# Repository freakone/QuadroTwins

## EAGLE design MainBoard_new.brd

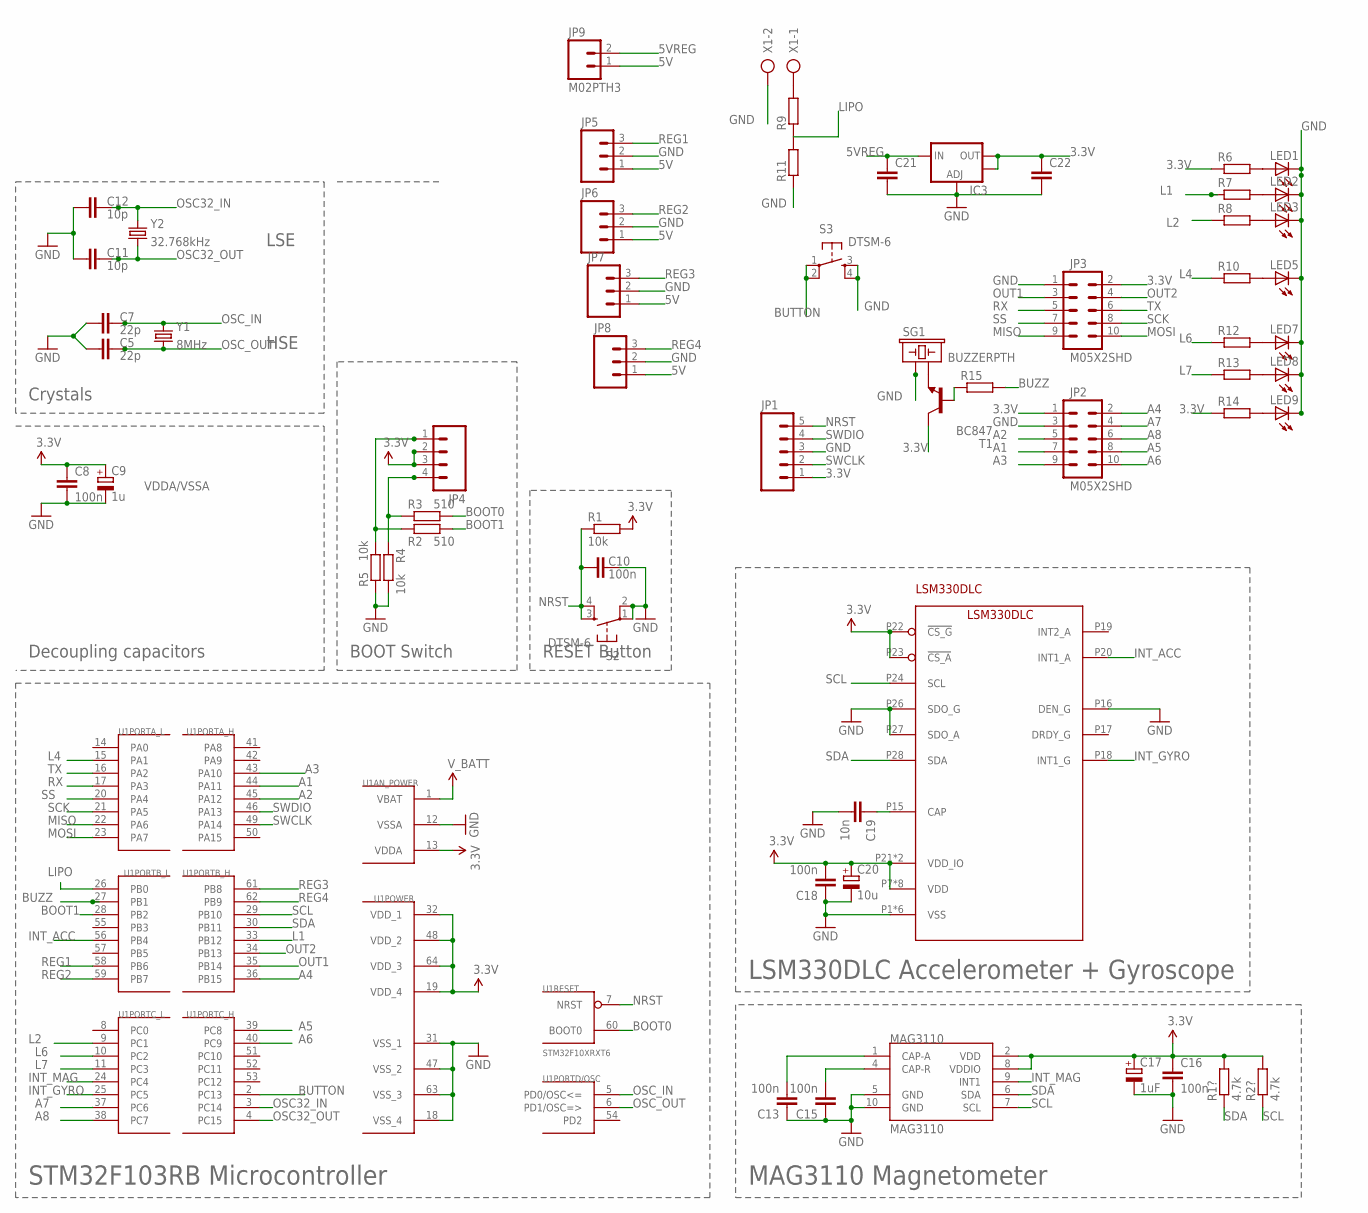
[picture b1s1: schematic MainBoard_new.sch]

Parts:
C5, C7: 22p; C0805
C8, C10, C13, C15, C16, C18: 100n; C0805
C9: 1u; SMC_A
C11, C12: 10p; C0805
C17: 1uF; SMC_A
C19: 10n; C0805
C20: 10u; SMC_A
C21, C22: C-EUC0805; C0805
IC3: V_REG_LM1117SOT223; SOT223
JP1: M05PTH_LONGPADS; 1X05_LONGPADS
JP2, JP3: M05X2SHD; 2X5-SHROUDED
JP4: M04LONGPADS; 1X04_LONGPADS
JP5, JP6, JP7, JP8: M03LONGPADS; 1X03_LONGPADS
JP9: M02PTH3; 1X02_LONGPADS
LED1, LED2, LED3, LED5, LED7, LED8, LED9: LEDCHIPLED_0805; CHIPLED_0805
LSM330DLC: LSM330DLC; LGA_4X5X1P1_28L
MAG3110: MAG3110; DFN-10
R1, R4, R5: 10k; R0805
R1?, R2?: 4.7k; R0805
R2, R3: 510; R0805
R6, R7, R8, R9, R10, R11, R12, R13, R14: R-EU_M0805; M0805
R15: R-EU_R0805; R0805
S2, S3: DTSM-6
SG1: BUZZERPTH; BUZZER-12MM
T1: BC847; SOT23
U1: STM32F10XRXT6; TQFP64
X1: AK300/2
Y1: 8MHz; HC49UP
Y2: 32.768kHz; CRYSTAL-32KHZ-SMD_EPSON_MC146

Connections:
3.3V: C8.1, C9.+, C16.1, C17.+, C18.2, C20.+, C22.1, IC3.2 (OUT), IC3.4 (OUT), JP1.1, JP2.1, JP3.2, JP4.2, JP4.3, LSM330DLC.P7 (VDD), LSM330DLC.P8 (VDD), LSM330DLC.P9 (VDD), LSM330DLC.P10 (VDD), LSM330DLC.P11 (VDD), LSM330DLC.P12 (VDD), LSM330DLC.P13 (VDD), LSM330DLC.P14 (VDD), LSM330DLC.P21 (VDD_IO), LSM330DLC.P22 (!CS_G), LSM330DLC.P23 (!CS_A), LSM330DLC.P25 (VDD_IO), MAG3110.2 (VDD), MAG3110.8 (VDDIO), R1.2, R1?.2, R2?.2, R6.1, R14.1, T1.3 (C), U1.13 (VDDA), U1.19 (VDD_4), U1.32 (VDD_1), U1.48 (VDD_2), U1.64 (VDD_3)
5V: JP5.1, JP6.1, JP7.1, JP8.1, JP9.1
5VREG: C21.1, IC3.3 (IN), JP9.2
A1: JP2.7, U1.44 (PA11)
A2: JP2.5, U1.45 (PA12)
A3: JP2.9, U1.43 (PA10)
A4: JP2.2, U1.36 (PB15)
A5: JP2.8, U1.39 (PC8)
A6: JP2.10, U1.40 (PC9)
A7: JP2.4, U1.37 (PC6)
A8: JP2.6, U1.38 (PC7)
BOOT0: R3.2, U1.60 (BOOT0)
BOOT1: R2.2, U1.28 (PB2)
BUTTON: S3.1, S3.2, U1.2 (PC13)
BUZZ: R15.2, U1.27 (PB1)
GND: C5.1, C7.1, C8.2, C9.-, C10.2, C11.1, C12.1, C13.1, C15.1, C16.2, C17.-, C18.1, C19.2, C20.-, C21.2, C22.2, IC3.1 (ADJ), JP1.3, JP2.3, JP3.1, JP5.2, JP6.2, JP7.2, JP8.2, LED1.C, LED2.C, LED3.C, LED5.C, LED7.C, LED8.C, LED9.C, LSM330DLC.P1 (VSS), LSM330DLC.P2 (VSS), LSM330DLC.P3 (VSS), LSM330DLC.P4 (VSS), LSM330DLC.P5 (VSS), LSM330DLC.P6 (VSS), LSM330DLC.P16 (DEN_G), LSM330DLC.P26 (SDO_G), LSM330DLC.P27 (SDO_A), MAG3110.5 (GND), MAG3110.10 (GND), R4.2, R5.1, R11.1, S2.1, S2.2, S3.3, S3.4, SG1.+ (1), U1.12 (VSSA), U1.18 (VSS_4), U1.31 (VSS_1), U1.47 (VSS_2), U1.63 (VSS_3), X1.2
INT_ACC: LSM330DLC.P20 (INT1_A), U1.56 (PB4)
INT_GYRO: LSM330DLC.P18 (INT1_G), U1.25 (PC5)
INT_MAG: MAG3110.9 (INT1), U1.24 (PC4)
L1: R7.1, U1.33 (PB12)
L2: R8.1, U1.9 (PC1)
L4: R10.1, U1.15 (PA1)
L6: R12.1, U1.10 (PC2)
L7: R13.1, U1.11 (PC3)
LIPO: R9.1, R11.2, U1.26 (PB0)
MISO: JP3.9, U1.22 (PA6)
MOSI: JP3.10, U1.23 (PA7)
unnamed: JP4.1, R2.1, R5.2
unnamed: JP4.4, R3.1, R4.1
unnamed: C15.2, MAG3110.4 (CAP-R)
unnamed: C13.2, MAG3110.1 (CAP-A)
unnamed: C19.1, LSM330DLC.P15 (CAP)
unnamed: LED1.A, R6.2
unnamed: LED2.A, R7.2
unnamed: LED3.A, R8.2
unnamed: LED5.A, R10.2
unnamed: LED7.A, R12.2
unnamed: LED8.A, R13.2
unnamed: LED9.A, R14.2
unnamed: SG1.- (2), T1.2 (E)
unnamed: R9.2, X1.1
unnamed: R15.1, T1.1 (B)
NRST: C10.1, JP1.5, R1.1, S2.3, S2.4, U1.7 (NRST)
OSC32_IN: C12.2, U1.3 (PC14), Y2.P$1 (2)
OSC32_OUT: C11.2, U1.4 (PC15), Y2.P$2 (1)
OSC_IN: C7.2, U1.5 (PD0/OSC<=), Y1.2
OSC_OUT: C5.2, U1.6 (PD1/OSC=>), Y1.1
OUT1: JP3.3, U1.35 (PB14)
OUT2: JP3.4, U1.34 (PB13)
REG1: JP5.3, U1.58 (PB6)
REG2: JP6.3, U1.59 (PB7)
REG3: JP7.3, U1.61 (PB8)
REG4: JP8.3, U1.62 (PB9)
RX: JP3.5, U1.17 (PA3)
SCK: JP3.8, U1.21 (PA5)
SCL: LSM330DLC.P24 (SCL), MAG3110.7 (SCL), R2?.1, U1.29 (PB10)
SDA: LSM330DLC.P28 (SDA), MAG3110.6 (SDA), R1?.1, U1.30 (PB11)
SS: JP3.7, U1.20 (PA4)
SWCLK: JP1.2, U1.49 (PA14)
SWDIO: JP1.4, U1.46 (PA13)
TX: JP3.6, U1.16 (PA2)
V_BATT: U1.1 (VBAT)

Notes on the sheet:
STM32F103RB Microcontroller
RESET Button
BOOT Switch
Decoupling capacitors
VDDA/VSSA
Crystals
HSE
LSE
MAG3110 Magnetometer
LSM330DLC Accelerometer + Gyroscope

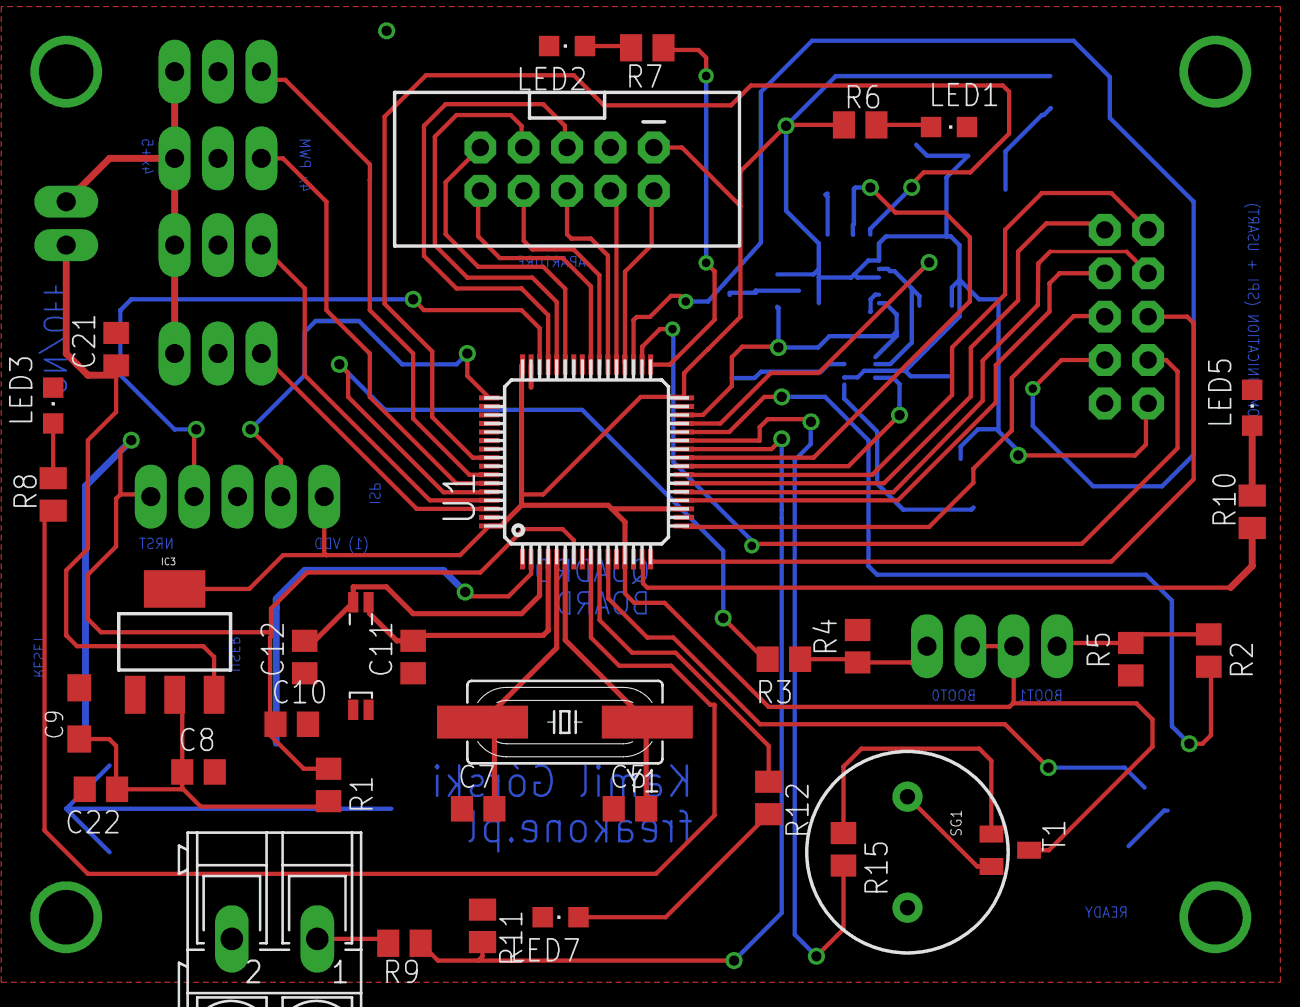
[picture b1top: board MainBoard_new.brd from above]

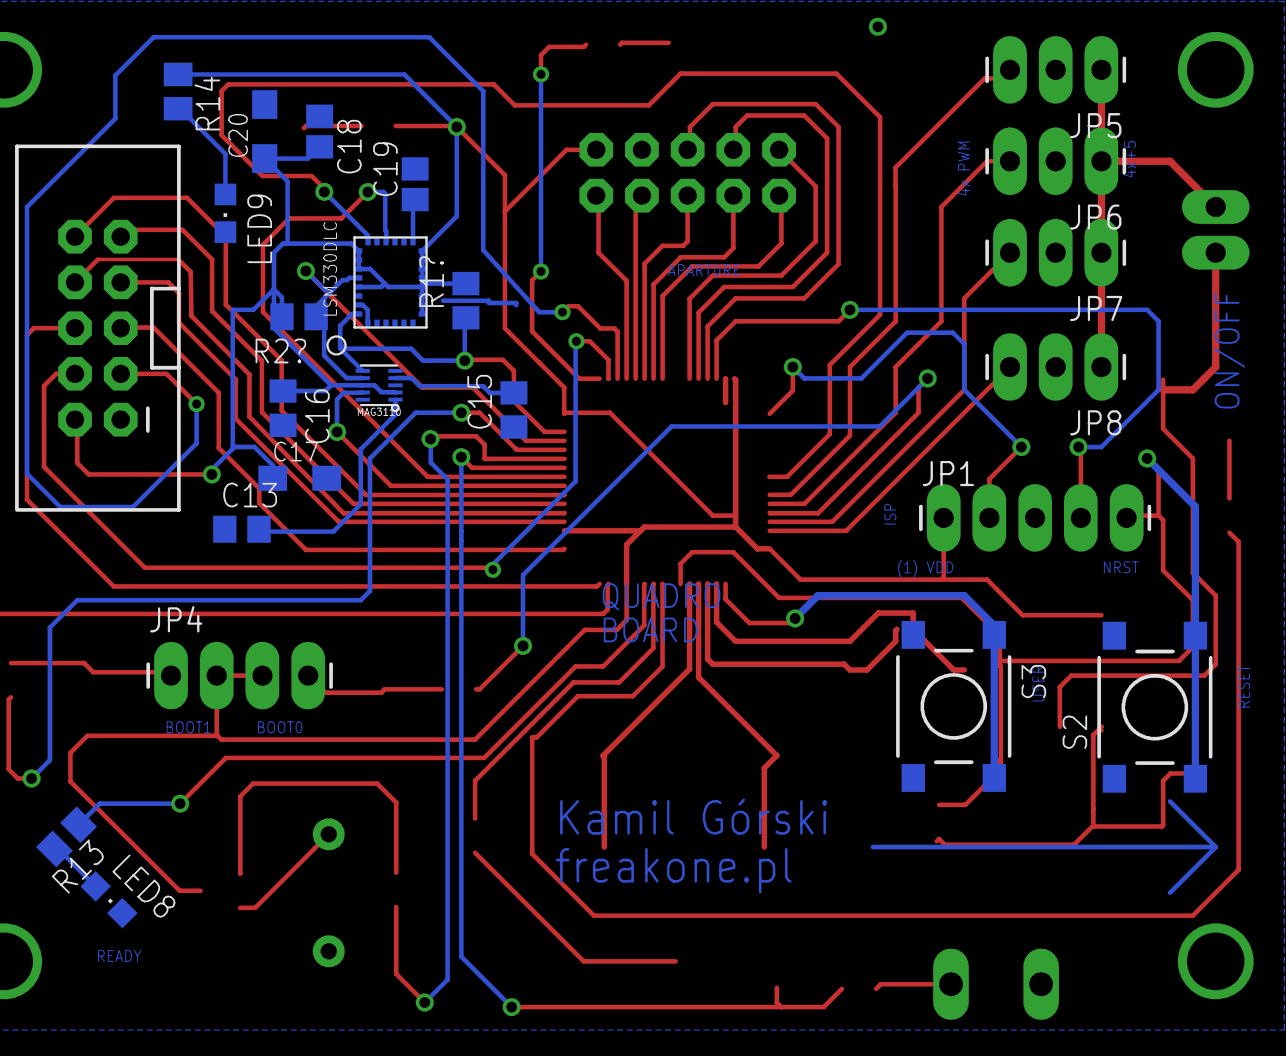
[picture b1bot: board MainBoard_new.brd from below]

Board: 2 copper layers, 60 parts (24 on the bottom side), 61 nets.

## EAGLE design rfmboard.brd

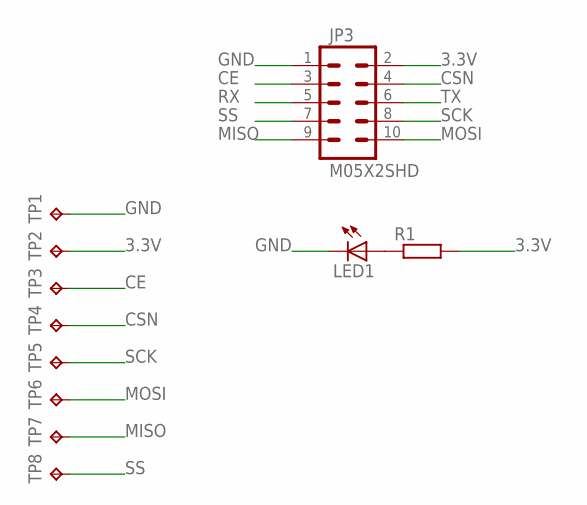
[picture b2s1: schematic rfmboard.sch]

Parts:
JP3: M05X2SHD; 2X5-SHROUDED
LED1: LEDSML0805; SML0805
R1: R-EU_R0805; R0805
TP1, TP2, TP3, TP4, TP5, TP6, TP7, TP8: TPB1,27; B1,27

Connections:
3.3V: JP3.2, R1.2, TP2.TP
CE: JP3.3, TP3.TP
CSN: JP3.4, TP4.TP
GND: JP3.1, LED1.C, TP1.TP
MISO: JP3.9, TP7.TP
MOSI: JP3.10, TP6.TP
unnamed: LED1.A, R1.1
RX: JP3.5
SCK: JP3.8, TP5.TP
SS: JP3.7, TP8.TP
TX: JP3.6

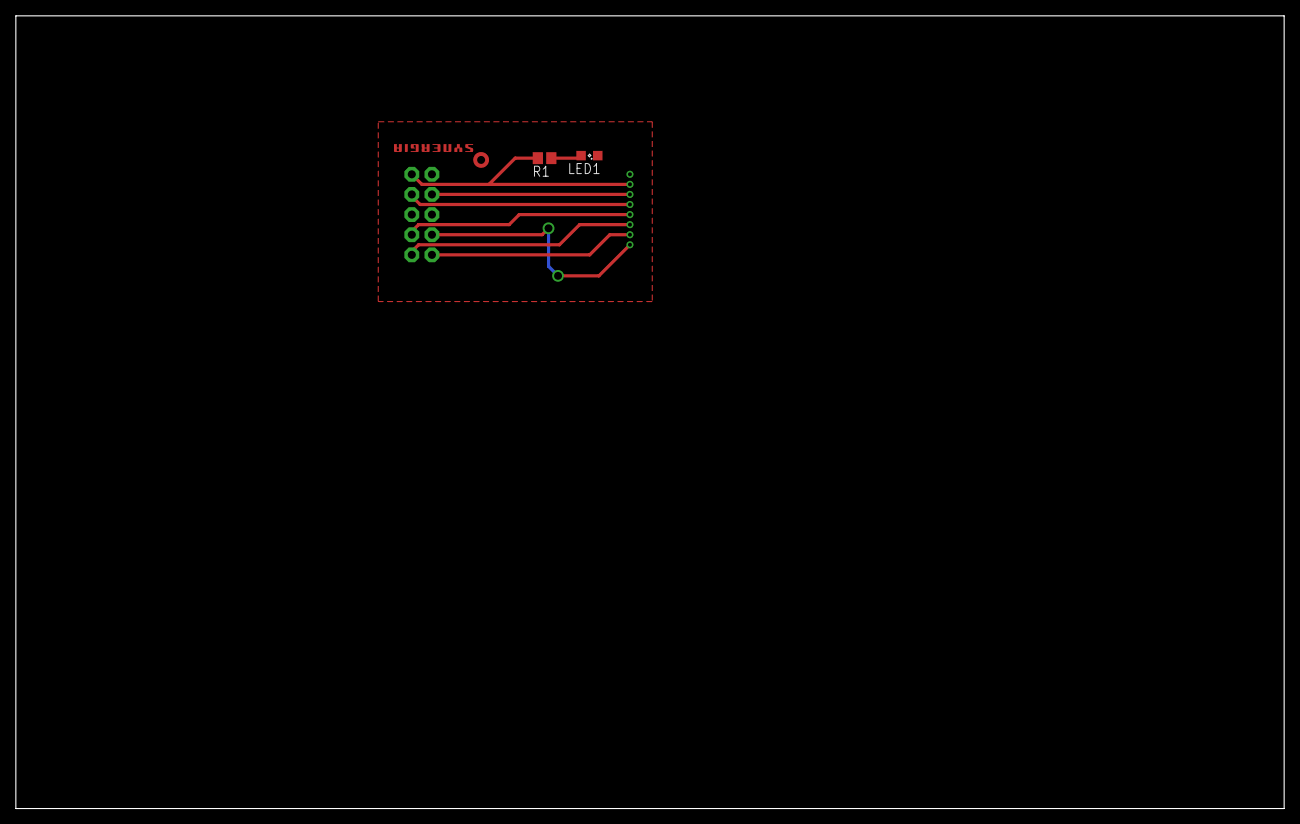
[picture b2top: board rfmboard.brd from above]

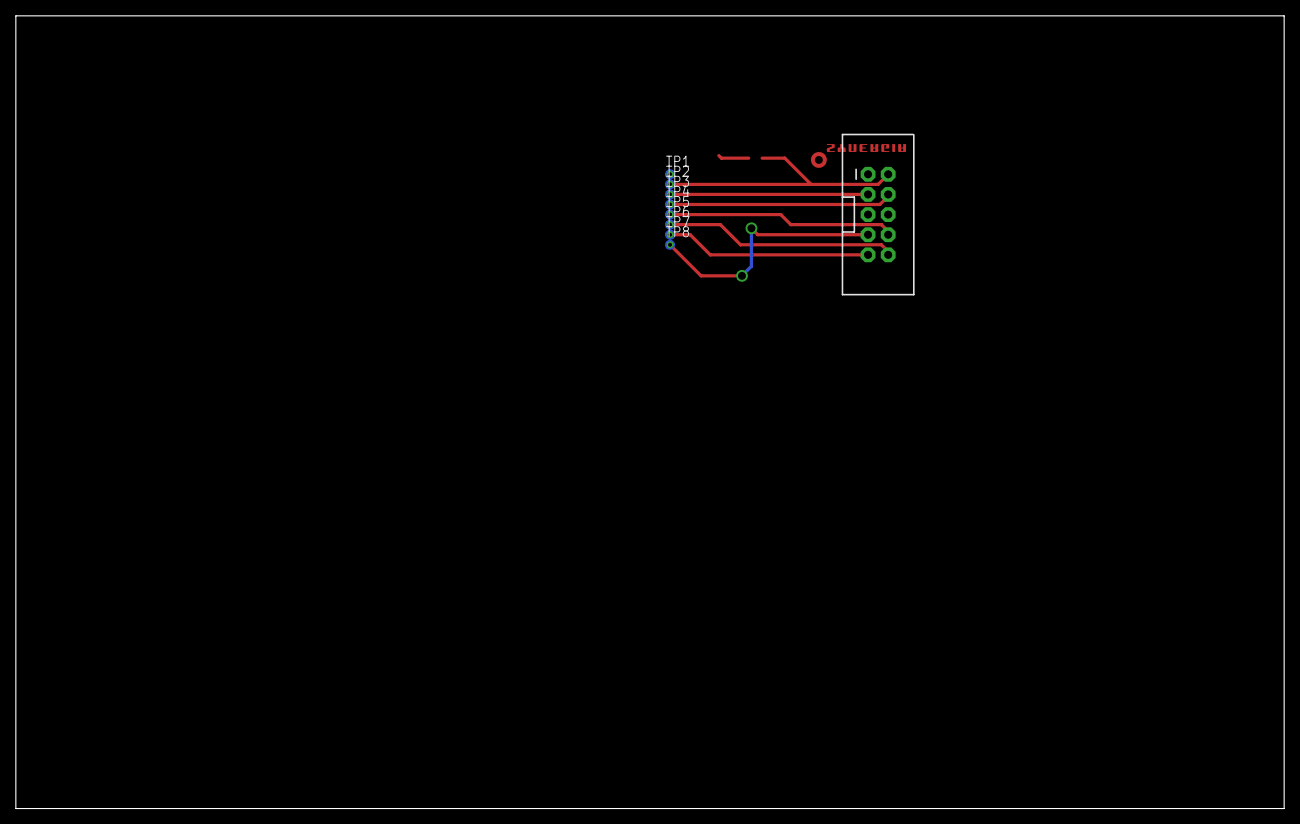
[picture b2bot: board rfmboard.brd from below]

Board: 2 copper layers, 160.0 x 100.0 mm, 12 parts (9 on the bottom side), 9 nets.

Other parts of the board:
U$1: SYNERGIA_12MM

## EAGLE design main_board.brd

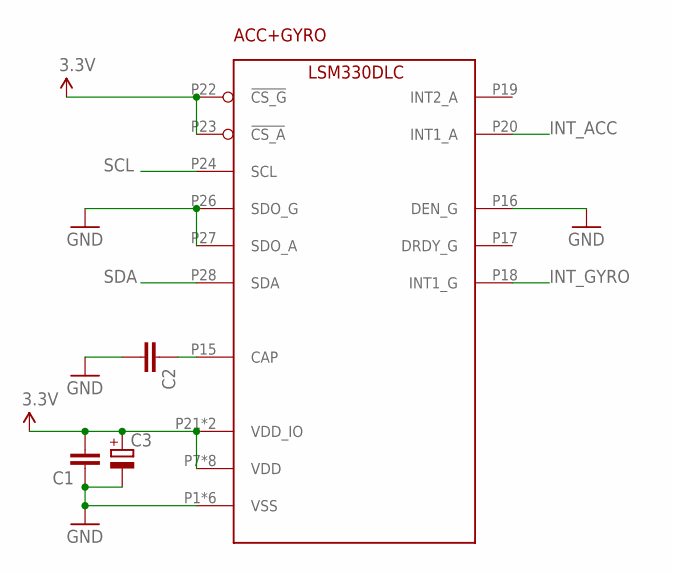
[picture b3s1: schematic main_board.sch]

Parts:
ACC+GYRO: LSM330DLC; LGA_4X5X1P1_28L
C1, C2: C-EUC0805; C0805
C3: CPOL-EUSMCA; SMC_A

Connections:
3.3V: ACC+GYRO.P7 (VDD), ACC+GYRO.P8 (VDD), ACC+GYRO.P9 (VDD), ACC+GYRO.P10 (VDD), ACC+GYRO.P11 (VDD), ACC+GYRO.P12 (VDD), ACC+GYRO.P13 (VDD), ACC+GYRO.P14 (VDD), ACC+GYRO.P21 (VDD_IO), ACC+GYRO.P22 (!CS_G), ACC+GYRO.P23 (!CS_A), ACC+GYRO.P25 (VDD_IO), C1.2, C3.+
GND: ACC+GYRO.P1 (VSS), ACC+GYRO.P2 (VSS), ACC+GYRO.P3 (VSS), ACC+GYRO.P4 (VSS), ACC+GYRO.P5 (VSS), ACC+GYRO.P6 (VSS), ACC+GYRO.P16 (DEN_G), ACC+GYRO.P26 (SDO_G), ACC+GYRO.P27 (SDO_A), C1.1, C2.2, C3.-
INT_ACC: ACC+GYRO.P20 (INT1_A)
INT_GYRO: ACC+GYRO.P18 (INT1_G)
unnamed: ACC+GYRO.P15 (CAP), C2.1
SCL: ACC+GYRO.P24 (SCL)
SDA: ACC+GYRO.P28 (SDA)

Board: 2 copper layers, 4 parts (0 on the bottom side), 3 nets, no tracks yet.

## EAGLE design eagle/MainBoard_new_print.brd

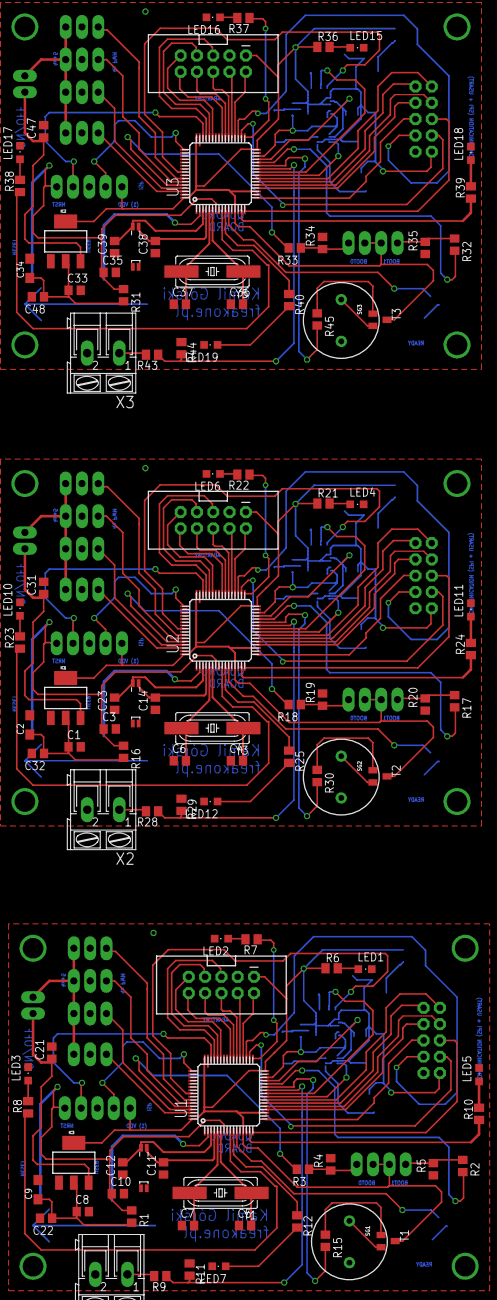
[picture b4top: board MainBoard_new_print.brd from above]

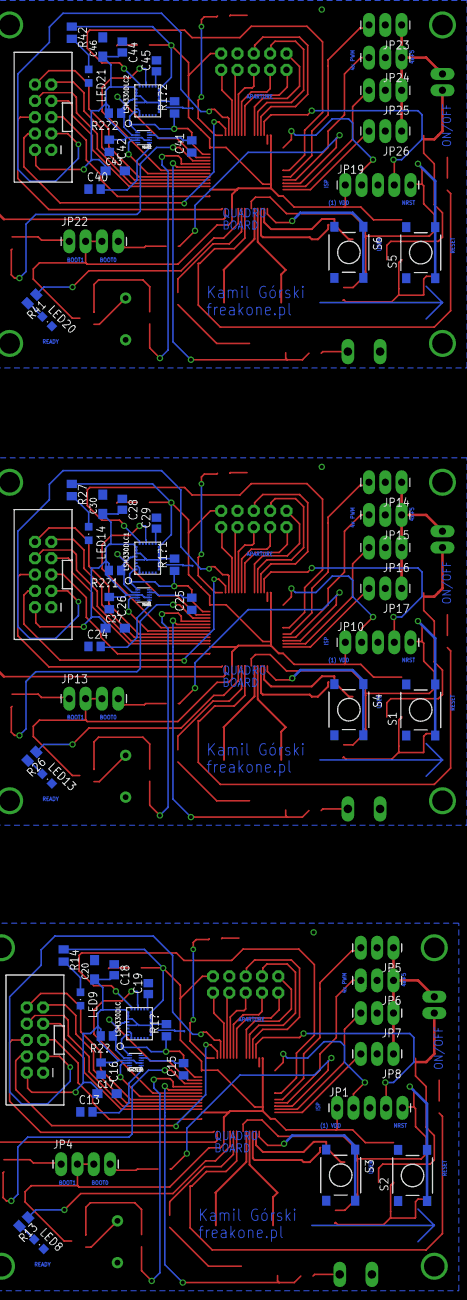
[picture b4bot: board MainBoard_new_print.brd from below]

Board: 2 copper layers, 181 parts (72 on the bottom side), 183 nets.

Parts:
C1, C3, C8, C10, C13, C15, C16, C18, C24, C25, C26, C28, C33, C35, C40, C41, C42, C44: 100n; C0805
C2, C9, C34: 1u; SMC_A
C4, C5, C6, C7, C36, C37: 22p; C0805
C11, C12, C14, C23, C38, C39: 10p; C0805
C17, C27, C43: 1uF; SMC_A
C19, C29, C45: 10n; C0805
C20, C30, C46: 10u; SMC_A
C21, C22, C31, C32, C47, C48: C0805
E$1: A4P-LOC
IC1, IC2, IC3: SOT223
JP1, JP10, JP19: 1X05_LONGPADS
JP2, JP3, JP11, JP12, JP20, JP21: M05X2SHD; 2X5-SHROUDED
JP4, JP13, JP22: 1X04_LONGPADS
JP5, JP6, JP7, JP8, JP14, JP15, JP16, JP17, JP23, JP24, JP25, JP26: 1X03_LONGPADS
JP9, JP18, JP27: M02PTH3; 1X02_LONGPADS
LED1, LED2, LED3, LED4, LED5, LED6, LED7, LED8, LED9, LED10, LED11, LED12, LED13, LED14, LED15, LED16, LED17, LED18, LED19, LED20, LED21: CHIPLED_0805
LSM330DLC, LSM330DLC1, LSM330DLC2: LSM330DLC; LGA_4X5X1P1_28L
MAG1, MAG2, MAG3110: MAG3110; DFN-10
R1, R4, R5, R16, R19, R20, R31, R34, R35: 10k; R0805
R1?, R1?1, R1?2, R2?, R2?1, R2?2: 4.7k; R0805
R2, R3, R17, R18, R32, R33: 510; R0805
R6, R7, R8, R9, R10, R11, R12, R13, R14, R21, R22, R23, R24, R25, R26, R27, R28, R29, R36, R37, R38, R39, R40, R41, R42, R43, R44: M0805
R15, R30, R45: R0805
S1, S2, S3, S4, S5, S6: DTSM-6
SG1, SG2, SG3: BUZZERPTH; BUZZER-12MM
T1, T2, T3: BC847; SOT23
U1, U2, U3: STM32F10XRXT6; TQFP64
X1, X2, X3: AK300/2
Y1, Y3, Y5: 8MHz; HC49UP
Y2, Y4, Y6: 32.768kHz; CRYSTAL-32KHZ-SMD_EPSON_MC146

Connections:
3.3V: C8.1, C9.+, C16.1, C17.+, C18.2, C20.+, C22.1, IC3.2, IC3.4, JP1.1, JP2.1, JP3.2, JP4.2, JP4.3, LSM330DLC.P7, LSM330DLC.P8, LSM330DLC.P9, LSM330DLC.P10, LSM330DLC.P11, LSM330DLC.P12, LSM330DLC.P13, LSM330DLC.P14, LSM330DLC.P21, LSM330DLC.P22, LSM330DLC.P23, LSM330DLC.P25, MAG3110.2, MAG3110.8, R1.2, R1?.2, R2?.2, R6.1, R14.1, T1.3, U1.13, U1.19, U1.32, U1.48, U1.64
3.3V1: C1.1, C2.+, C26.1, C27.+, C28.2, C30.+, C32.1, IC1.2, IC1.4, JP10.1, JP11.1, JP12.2, JP13.2, JP13.3, LSM330DLC1.P7, LSM330DLC1.P8, LSM330DLC1.P9, LSM330DLC1.P10, LSM330DLC1.P11, LSM330DLC1.P12, LSM330DLC1.P13, LSM330DLC1.P14, LSM330DLC1.P21, LSM330DLC1.P22, LSM330DLC1.P23, LSM330DLC1.P25, MAG1.2, MAG1.8, R1?1.2, R2?1.2, R16.2, R21.1, R27.1, T2.3, U2.13, U2.19, U2.32, U2.48, U2.64
3.3V2: C33.1, C34.+, C42.1, C43.+, C44.2, C46.+, C48.1, IC2.2, IC2.4, JP19.1, JP20.1, JP21.2, JP22.2, JP22.3, LSM330DLC2.P7, LSM330DLC2.P8, LSM330DLC2.P9, LSM330DLC2.P10, LSM330DLC2.P11, LSM330DLC2.P12, LSM330DLC2.P13, LSM330DLC2.P14, LSM330DLC2.P21, LSM330DLC2.P22, LSM330DLC2.P23, LSM330DLC2.P25, MAG2.2, MAG2.8, R1?2.2, R2?2.2, R31.2, R36.1, R42.1, T3.3, U3.13, U3.19, U3.32, U3.48, U3.64
5V: JP5.1, JP6.1, JP7.1, JP8.1, JP9.1
5V1: JP14.1, JP15.1, JP16.1, JP17.1, JP18.1
5V2: JP23.1, JP24.1, JP25.1, JP26.1, JP27.1
5VREG: C21.1, IC3.3, JP9.2
5VREG1: C31.1, IC1.3, JP18.2
5VREG2: C47.1, IC2.3, JP27.2
A1: JP2.7, U1.44
A2: JP2.5, U1.45
A3: JP2.9, U1.43
A4: JP2.2, U1.36
A5: JP2.8, U1.39
A6: JP2.10, U1.40
A7: JP2.4, U1.37
A8: JP2.6, U1.38
A9: JP11.2, U2.36
A10: JP11.8, U2.39
A11: JP11.10, U2.40
A12: JP11.4, U2.37
A13: JP11.6, U2.38
A14: JP11.7, U2.44
A15: JP11.5, U2.45
A16: JP11.9, U2.43
A17: JP20.2, U3.36
A18: JP20.8, U3.39
A19: JP20.10, U3.40
A20: JP20.4, U3.37
A21: JP20.6, U3.38
A22: JP20.7, U3.44
A23: JP20.5, U3.45
A24: JP20.9, U3.43
BOOT0: R3.2, U1.60
BOOT1: R2.2, U1.28
BOOT2: R18.2, U2.60
BOOT3: R17.2, U2.28
BOOT4: R33.2, U3.60
BOOT5: R32.2, U3.28
BUTTON: S3.1, S3.2, U1.2
BUTTON1: S4.1, S4.2, U2.2
BUTTON2: S6.1, S6.2, U3.2
BUZZ: R15.2, U1.27
BUZZ1: R30.2, U2.27
BUZZ2: R45.2, U3.27
GND: C5.1, C7.1, C8.2, C9.-, C10.2, C11.1, C12.1, C13.1, C15.1, C16.2, C17.-, C18.1, C19.2, C20.-, C21.2, C22.2, IC3.1, JP1.3, JP2.3, JP3.1, JP5.2, JP6.2, JP7.2, JP8.2, LED1.C, LED2.C, LED3.C, LED5.C, LED7.C, LED8.C, LED9.C, LSM330DLC.P1, LSM330DLC.P2, LSM330DLC.P3, LSM330DLC.P4, LSM330DLC.P5, LSM330DLC.P6, LSM330DLC.P16, LSM330DLC.P26, LSM330DLC.P27, MAG3110.5, MAG3110.10, R4.2, R5.1, R11.1, S2.1, S2.2, S3.3, S3.4, SG1.+, U1.12, U1.18, U1.31, U1.47, U1.63, X1.2
GND1: C1.2, C2.-, C3.2, C4.1, C6.1, C14.1, C23.1, C24.1, C25.1, C26.2, C27.-, C28.1, C29.2, C30.-, C31.2, C32.2, IC1.1, JP10.3, JP11.3, JP12.1, JP14.2, JP15.2, JP16.2, JP17.2, LED4.C, LED6.C, LED10.C, LED11.C, LED12.C, LED13.C, LED14.C, LSM330DLC1.P1, LSM330DLC1.P2, LSM330DLC1.P3, LSM330DLC1.P4, LSM330DLC1.P5, LSM330DLC1.P6, LSM330DLC1.P16, LSM330DLC1.P26, LSM330DLC1.P27, MAG1.5, MAG1.10, R19.2, R20.1, R29.1, S1.1, S1.2, S4.3, S4.4, SG2.+, U2.12, U2.18, U2.31, U2.47, U2.63, X2.2
GND2: C33.2, C34.-, C35.2, C36.1, C37.1, C38.1, C39.1, C40.1, C41.1, C42.2, C43.-, C44.1, C45.2, C46.-, C47.2, C48.2, IC2.1, JP19.3, JP20.3, JP21.1, JP23.2, JP24.2, JP25.2, JP26.2, LED15.C, LED16.C, LED17.C, LED18.C, LED19.C, LED20.C, LED21.C, LSM330DLC2.P1, LSM330DLC2.P2, LSM330DLC2.P3, LSM330DLC2.P4, LSM330DLC2.P5, LSM330DLC2.P6, LSM330DLC2.P16, LSM330DLC2.P26, LSM330DLC2.P27, MAG2.5, MAG2.10, R34.2, R35.1, R44.1, S5.1, S5.2, S6.3, S6.4, SG3.+, U3.12, U3.18, U3.31, U3.47, U3.63, X3.2
INT_ACC: LSM330DLC.P20, U1.56
INT_ACC1: LSM330DLC1.P20, U2.56
INT_ACC2: LSM330DLC2.P20, U3.56
INT_GYRO: LSM330DLC.P18, U1.25
INT_GYRO1: LSM330DLC1.P18, U2.25
INT_GYRO2: LSM330DLC2.P18, U3.25
INT_MAG: MAG3110.9, U1.24
INT_MAG1: MAG1.9, U2.24
INT_MAG2: MAG2.9, U3.24
L1: R7.1, U1.33
L2: R8.1, U1.9
L3: R23.1, U2.9
L4: R10.1, U1.15
L5: R24.1, U2.15
L6: R12.1, U1.10
L7: R13.1, U1.11
L8: R25.1, U2.10
L9: R26.1, U2.11
L10: R22.1, U2.33
L11: R38.1, U3.9
L12: R39.1, U3.15
L13: R40.1, U3.10
L14: R41.1, U3.11
L15: R37.1, U3.33
LIPO: R9.1, R11.2, U1.26
LIPO1: R28.1, R29.2, U2.26
LIPO2: R43.1, R44.2, U3.26
MISO: JP3.9, U1.22
MISO1: JP12.9, U2.22
MISO2: JP21.9, U3.22
MOSI: JP3.10, U1.23
MOSI1: JP12.10, U2.23
MOSI2: JP21.10, U3.23
unnamed: JP4.1, R2.1, R5.2
unnamed: JP4.4, R3.1, R4.1
unnamed: C15.2, MAG3110.4
unnamed: C13.2, MAG3110.1
unnamed: C19.1, LSM330DLC.P15
unnamed: LED1.A, R6.2
unnamed: LED2.A, R7.2
unnamed: LED3.A, R8.2
unnamed: LED5.A, R10.2
unnamed: LED7.A, R12.2
unnamed: LED8.A, R13.2
unnamed: LED9.A, R14.2
unnamed: SG1.-, T1.2
unnamed: R9.2, X1.1
unnamed: R15.1, T1.1
unnamed: JP13.1, R17.1, R20.2
unnamed: JP13.4, R18.1, R19.1
unnamed: C25.2, MAG1.4
unnamed: C24.2, MAG1.1
unnamed: C29.1, LSM330DLC1.P15
unnamed: LED4.A, R21.2
unnamed: LED6.A, R22.2
unnamed: LED10.A, R23.2
unnamed: LED11.A, R24.2
unnamed: LED12.A, R25.2
unnamed: LED13.A, R26.2
unnamed: LED14.A, R27.2
unnamed: R28.2, X2.1
unnamed: SG2.-, T2.2
unnamed: R30.1, T2.1
unnamed: JP22.1, R32.1, R35.2
unnamed: JP22.4, R33.1, R34.1
unnamed: C41.2, MAG2.4
unnamed: C40.2, MAG2.1
unnamed: C45.1, LSM330DLC2.P15
unnamed: LED15.A, R36.2
unnamed: LED16.A, R37.2
unnamed: LED17.A, R38.2
unnamed: LED18.A, R39.2
unnamed: LED19.A, R40.2
unnamed: LED20.A, R41.2
unnamed: LED21.A, R42.2
unnamed: R43.2, X3.1
unnamed: SG3.-, T3.2
unnamed: R45.1, T3.1
NRST: C10.1, JP1.5, R1.1, S2.3, S2.4, U1.7
NRST1: C3.1, JP10.5, R16.1, S1.3, S1.4, U2.7
NRST2: C35.1, JP19.5, R31.1, S5.3, S5.4, U3.7
OSC32_IN: C12.2, U1.3, Y2.P$1
OSC32_IN1: C23.2, U2.3, Y4.P$1
OSC32_IN2: C39.2, U3.3, Y6.P$1
OSC32_OUT: C11.2, U1.4, Y2.P$2
OSC32_OUT1: C14.2, U2.4, Y4.P$2
OSC32_OUT2: C38.2, U3.4, Y6.P$2
OSC_IN: C7.2, U1.5, Y1.2
OSC_IN1: C6.2, U2.5, Y3.2
OSC_IN2: C37.2, U3.5, Y5.2
OSC_OUT: C5.2, U1.6, Y1.1
OSC_OUT1: C4.2, U2.6, Y3.1
OSC_OUT2: C36.2, U3.6, Y5.1
OUT1: JP3.3, U1.35
OUT2: JP3.4, U1.34
OUT3: JP12.3, U2.35
OUT4: JP12.4, U2.34
OUT5: JP21.3, U3.35
OUT6: JP21.4, U3.34
REG1: JP5.3, U1.58
REG2: JP6.3, U1.59
REG3: JP7.3, U1.61
REG4: JP8.3, U1.62
REG5: JP14.3, U2.58
REG6: JP15.3, U2.59
REG7: JP16.3, U2.61
REG8: JP17.3, U2.62
REG9: JP23.3, U3.58
REG10: JP24.3, U3.59
REG11: JP25.3, U3.61
REG12: JP26.3, U3.62
RX: JP3.5, U1.17
RX1: JP12.5, U2.17
RX2: JP21.5, U3.17
SCK: JP3.8, U1.21
SCK1: JP12.8, U2.21
SCK2: JP21.8, U3.21
SCL: LSM330DLC.P24, MAG3110.7, R2?.1, U1.29
SCL1: LSM330DLC1.P24, MAG1.7, R2?1.1, U2.29
SCL2: LSM330DLC2.P24, MAG2.7, R2?2.1, U3.29
SDA: LSM330DLC.P28, MAG3110.6, R1?.1, U1.30
SDA1: LSM330DLC1.P28, MAG1.6, R1?1.1, U2.30
SDA2: LSM330DLC2.P28, MAG2.6, R1?2.1, U3.30
SS: JP3.7, U1.20
SS1: JP12.7, U2.20
SS2: JP21.7, U3.20
SWCLK: JP1.2, U1.49
SWCLK1: JP10.2, U2.49
SWCLK2: JP19.2, U3.49
SWDIO: JP1.4, U1.46
SWDIO1: JP10.4, U2.46
SWDIO2: JP19.4, U3.46
TX: JP3.6, U1.16
TX1: JP12.6, U2.16
TX2: JP21.6, U3.16

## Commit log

2013-02-08 zaczynamy zabawę!
2013-02-08 lsm330 skonczony
2013-02-08 wartosci w lsm i schemat zigbee
2013-02-09 porzadki w plikach
2013-02-09 dodane obwodki z nazwami dla poszczegolnych elementow
2013-02-19 schemat STMa i pliki płytki PCB
2013-07-10 płytka
2013-07-11 buzzer i adc
2013-07-11 poprawki
2013-07-29 zmniejszona płytka
2013-07-30 kompresja płytki, dodany npn do buzzera
2013-08-06 kosmetyka
2013-08-08 zgubione sygnały przerwań
2013-08-10 płytka gotowa, zaczynamy z kodem
2013-08-10 adc + dma
2013-08-12 odczyt z czujników
2013-08-14 początek oblicznia kąta
2013-08-15 regulator, odczyt throttle z aparatury
2013-08-16 program do pierwszych testów
2013-08-17 poprawki płytki, kodzik
2013-08-18 regulator dla drugiej osi + protokół na usarta
2013-08-18 poprawki, apka na komputer
2013-08-18 dodany barometr
2013-08-18 likwidacja zbetnych przelotek do satlandu
2013-12-16 przeróbki, poprawka algorytmów

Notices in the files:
parts and their libraries:
SparkFun-Electromechanical: Licensing: CC v3.0 Share-Alike You are welcome to use this library for commercial purposes.
